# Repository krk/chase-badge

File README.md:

# chase-badge

Designed using [KiCad](https://kicad-pcb.org/).

I tried to follow datasheet recommendations and tried to base the design on application note schematics and PCB layouts of the active components.

First revision of the board in the repo is rev-8. Earlier revisions are not available in this repo.

Schematics contain notes and all components should have their datasheet in their details in KiCAD.

### Kudos

- to [@smcatala](https://github.com/smcatala) for reviewing the designs!

### Connectors

1. USB-C for power, charging and with bootloader programming.
2. FPC 4-pin for add-on boards.
3. Li-Po JST-SH 2-pin.

### Used ICs

##### ATTINY85V-20SU

- Chosen over ATTINY85V-10SU so we may support [bit-banged USB protocol](https://www.obdev.at/products/vusb/index.html) for programming the badge only with a USB cable. [datasheet](http://ww1.microchip.com/downloads/en/DeviceDoc/atmel-2586-avr-8-bit-microcontroller-attiny25-attiny45-attiny85_datasheet.pdf).

##### TLC6C9512PWR shift register

Chosen for low power consumption and low parts count. [datasheet](http://www.ti.com/lit/ds/symlink/tlc6c5912.pdf).

#### TPS63000 buck-boost regulator

[datasheet](http://www.ti.com/lit/ds/symlink/tps63000.pdf)

#### MCP73837-FCI_UN battery charge manager

[datasheet](http://ww1.microchip.com/downloads/en/DeviceDoc/20002071C.pdf)

### Tested

- Programming ATtiny85 with [Tiny AVR Programmer](https://www.sparkfun.com/products/11801)
- ATtiny85, TLC6C9512 and LEDs can work as expected when powered externally
- 3.3V or 5V is supported.

### Untested

- Power regulator
- Battery charge manager
- XSIG1 external signal, for supporting a buzzer, microphone etc.
- USB bootloader and programming from USB cable.

### TODO

1. Test everything under "untested" above.
2. Determine Li-Po battery size.

### PCB renders of rev-8

Note that some footprints are missing from the renders.

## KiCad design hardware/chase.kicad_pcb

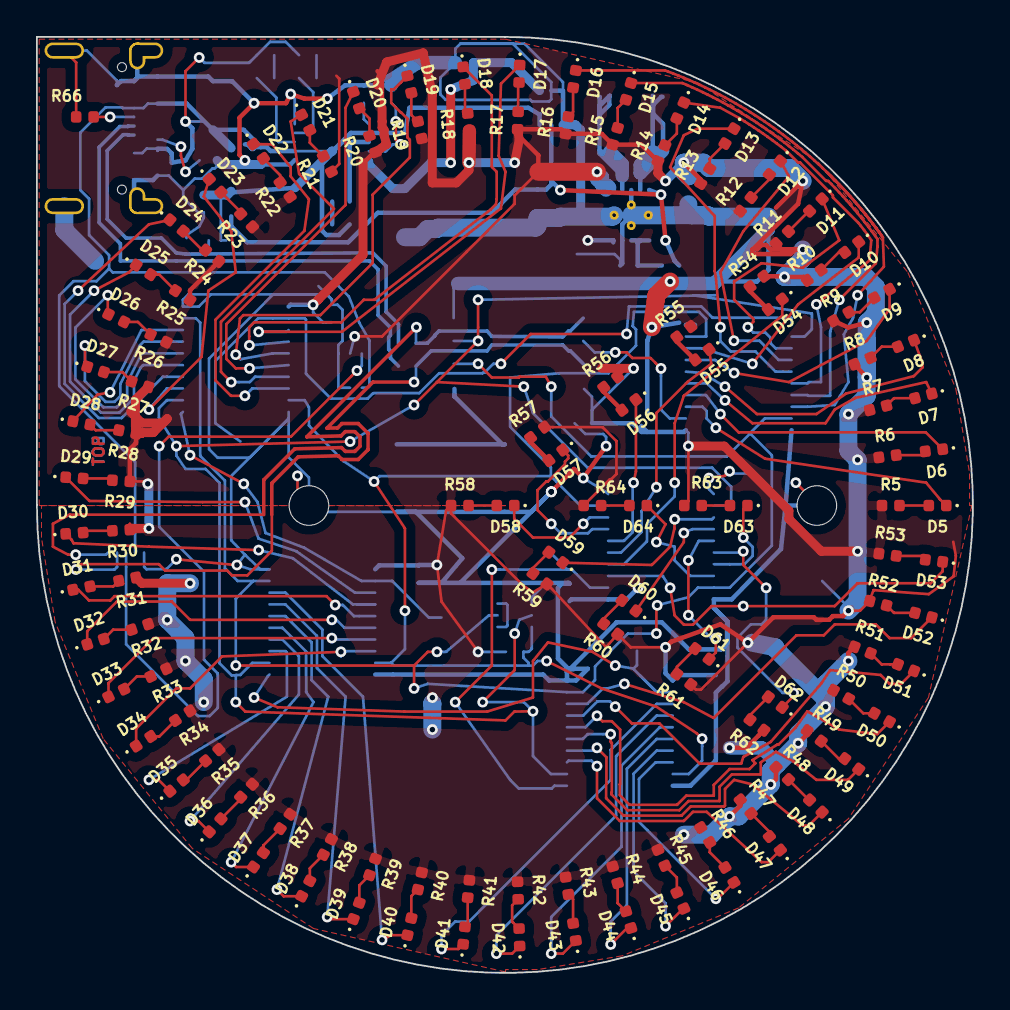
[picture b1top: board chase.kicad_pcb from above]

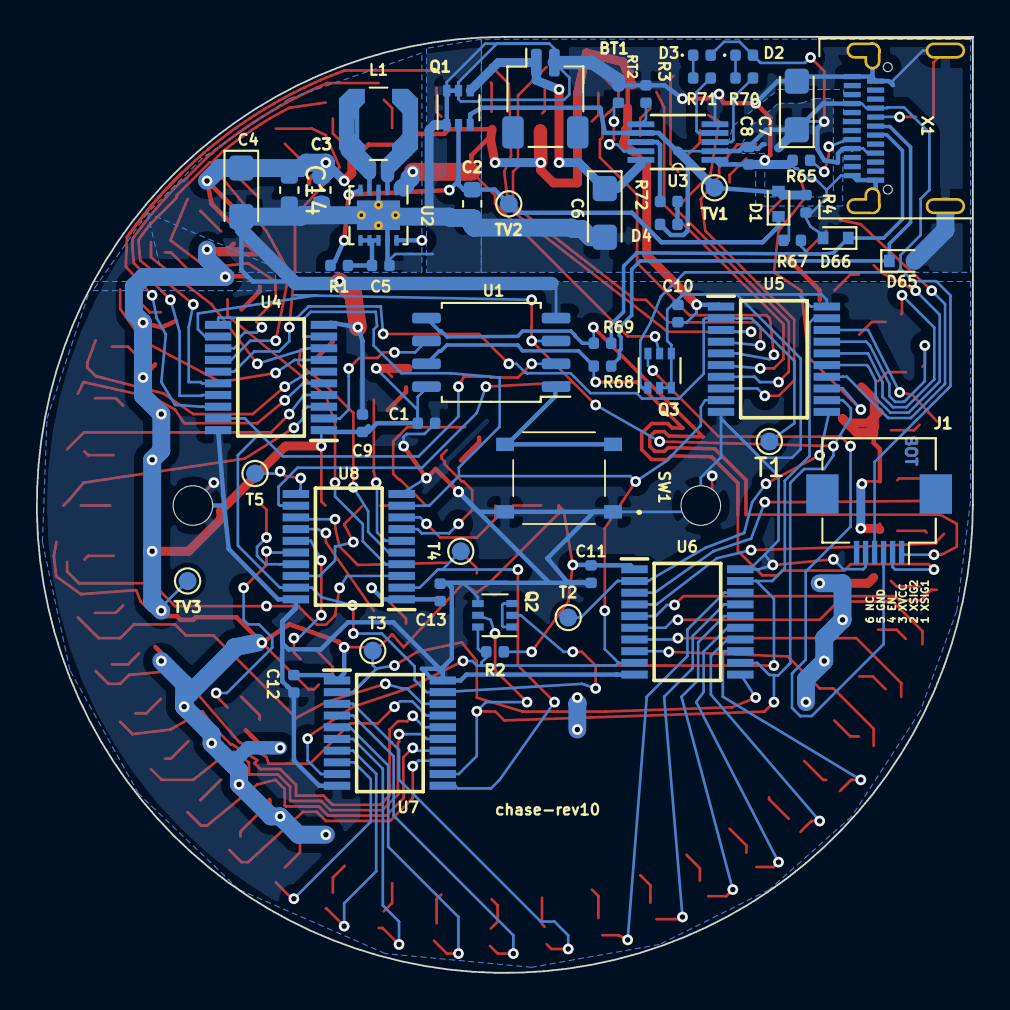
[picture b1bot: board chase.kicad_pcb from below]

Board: 2 copper layers, 52.0 x 52.0 mm, 179 parts (56 on the bottom side), 154 nets.

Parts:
BT1: Battery_Cell; JST_SH_SM02B-SRSS-TB_1x02-1MP_P1.00mm_Horizontal
C1, C5, C8, C9, C10, C11, C12, C13: 100n; C_0402_1005Metric
C2, C3, C14: 10uF; C_0603_1608Metric
C4, C6, C7: 47uF; CP_EIA-3216-18_Kemet-A
D1: D; D_SOD-523
D2, D3, D4, D5, D6, D7, D8, D9, D10, D11, D12, D13, D14, D15, D16, D17, D18, D19, D20, D21, D22, D23, D24, D25, D26, D27, D28, D29, D30, D31, D32, D33, D34, D35, D36, D37, D38, D39, D40, D41, D42, D43, D44, D45, D46, D47, D48, D49, D50, D51, D52, D53, D54, D55, D56, D57, D58, D59, D60, D61, D62, D63, D64: LED; LED_0402_1005Metric
D65, D66: 3V6; D_SOD-523
H1, H2: MountingHole_Pad; MountingHole_2.2mm_M2_ISO7380
J1: FH12-6S-0.5SH(55); Hirose_FH12-6S-0.5SH_1x06-1MP_P0.50mm_Horizontal
L1: 2.2uH; L_Coilcraft_LPS4018
Q1: DMC3400SDW-7; SOT-363_SC-70-6
Q2, Q3: DMN61D9UDW; SOT-363_SC-70-6
R1: 100; R_0402_1005Metric
R2, R5, R6, R7, R8, R9, R10, R11, R12, R13, R14, R15, R16, R17, R18, R19, R20, R21, R22, R23, R24, R25, R26, R27, R28, R29, R30, R31, R32, R33, R34, R35, R36, R37, R38, R39, R40, R41, R42, R43, R44, R45, R46, R47, R48, R49, R50, R51, R52, R53, R54, R55, R56, R57, R58, R59, R60, R61, R62, R63, R64, R70, R71, R72: 430; R_0402_1005Metric
R3: 1K; R_0402_1005Metric
R4: 100K; R_0402_1005Metric
R65, R66: 5.1K; R_0402_1005Metric
R67: 1K5; R_0402_1005Metric
R68, R69: 75.1; R_0402_1005Metric
RT2: 10K; R_0402_1005Metric
SW1: TS-1187A-B-A-B; TS1187ABAB
T1, T2, T3, T4, T5: TestPoint; TestPoint_Pad_D1.0mm
TV1, TV2, TV3: TestPoint; TestPoint_Pad_D1.0mm
U1: ATtiny85V; SOIC-8_5.275x5.275mm_P1.27mm
U2: TPS63000; Texas_DRC0010J_ThermalVias
U3: MCP73837-FCI_UN; SOP50P490X110-8N
U4, U5, U6, U7, U8: TLC6C5912GQPWRQ1; SOP65P640X120-20N
X1: USB3.1_TYPEC; Type-C_3.1_24P

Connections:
/LED Driver 1/RCK: Q2.5, U1.3, U4.12, U5.12, U6.12, U7.12, U8.12
/LED Driver 1/SER_IN: U1.6, U4.2
/LED Driver 1/SRCK: Q2.2, U1.2, U4.19, U5.19, U6.19, U7.19, U8.19
/LED Driver 1/~CLR: Q2.6, R2.1, U4.9, U5.9, U6.9, U7.9, U8.9
/LED Driver 2/SER_IN: T1.1, U4.11, U5.2
/LED Driver 3/SER_IN: T2.1, U5.11, U6.2
/LED Driver 4/SER_IN: T3.1, U6.11, U7.2
/LED Driver 5/SER_IN: T4.1, U7.11, U8.2
/LED Driver 5/SER_OUT: T5.1, U8.11
/USBD+: D65.1, R68.2, X1.B6
/USBD-: D66.1, R67.1, R69.2, X1.B7
D+: J1.2, R68.1, U1.7
D-: J1.1, R69.1, U1.5
GND: BT1.2, C1.2, C2.2, C3.2, C4.2, C5.1, C6.2, C7.2, C8.1, C9.1, C10.1, C11.1, C12.1, C13.1, C14.2, D65.2, D66.2, H1.1, H2.1, J1.5, Q1.1, Q1.5, Q1.6, Q2.4, Q3.2, Q3.3, Q3.4, R3.2, R4.1, R65.1, R66.1, RT2.1, SW1.A1, SW1.B1, U1.4, U2.3, U2.9, U2.11, U3.1, U3.5, U4.10, U4.20, U5.10, U5.20, U6.10, U6.20, U7.10, U7.20, U8.10, U8.20, X1.A1, X1.A12, X1.B1, X1.B12, X1.SHELL
unnamed: BT1.1, C6.1, Q1.4, U3.10
unnamed: C5.2, R1.1, U2.6, U2.7, U2.8
unnamed: D2.1, R70.2
unnamed: D3.1, R71.2
unnamed: D4.1, R72.2
unnamed: D5.1, U4.3
unnamed: D5.2, R5.2
unnamed: D6.1, U4.4
unnamed: D6.2, R6.2
unnamed: D7.1, U4.5
unnamed: D7.2, R7.2
unnamed: D8.1, U4.6
unnamed: D8.2, R8.2
unnamed: D9.1, U4.7
unnamed: D9.2, R9.2
unnamed: D10.1, U4.8
unnamed: D10.2, R10.2
unnamed: D11.1, U4.13
unnamed: D11.2, R11.2
unnamed: D12.1, U4.14
unnamed: D12.2, R12.2
unnamed: D13.1, U4.15
unnamed: D13.2, R13.2
unnamed: D14.1, U4.16
unnamed: D14.2, R14.2
unnamed: D15.1, U4.17
unnamed: D15.2, R15.2
unnamed: D16.1, U4.18
unnamed: D16.2, R16.2
unnamed: D17.1, U5.3
unnamed: D17.2, R17.2
unnamed: D18.1, U5.4
unnamed: D18.2, R18.2
unnamed: D19.1, U5.5
unnamed: D19.2, R19.2
unnamed: D20.1, U5.6
unnamed: D20.2, R20.2
unnamed: D21.1, U5.7
unnamed: D21.2, R21.2
unnamed: D22.1, U5.8
unnamed: D22.2, R22.2
unnamed: D23.1, U5.13
unnamed: D23.2, R23.2
unnamed: D24.1, U5.14
unnamed: D24.2, R24.2
unnamed: D25.1, U5.15
unnamed: D25.2, R25.2
unnamed: D26.1, U5.16
unnamed: D26.2, R26.2
unnamed: D27.1, U5.17
unnamed: D27.2, R27.2
unnamed: D28.1, U5.18
unnamed: D28.2, R28.2
unnamed: D29.1, U6.3
unnamed: D29.2, R29.2
unnamed: D30.1, U6.4
unnamed: D30.2, R30.2
unnamed: D31.1, U6.5
unnamed: D31.2, R31.2
unnamed: D32.1, U6.6
unnamed: D32.2, R32.2
unnamed: D33.1, U6.7
unnamed: D33.2, R33.2
unnamed: D34.1, U6.8
unnamed: D34.2, R34.2
unnamed: D35.1, U6.13
unnamed: D35.2, R35.2
unnamed: D36.1, U6.14
unnamed: D36.2, R36.2
unnamed: D37.1, U6.15
unnamed: D37.2, R37.2
unnamed: D38.1, U6.16
unnamed: D38.2, R38.2
unnamed: D39.1, U6.17
unnamed: D39.2, R39.2
unnamed: D40.1, U6.18
unnamed: D40.2, R40.2
unnamed: D41.1, U7.3
unnamed: D41.2, R41.2
unnamed: D42.1, U7.4
unnamed: D42.2, R42.2
unnamed: D43.1, U7.5
unnamed: D43.2, R43.2
unnamed: D44.1, U7.6
unnamed: D44.2, R44.2
unnamed: D45.1, U7.7
unnamed: D45.2, R45.2
unnamed: D46.1, U7.8
unnamed: D46.2, R46.2
unnamed: D47.1, U7.13
unnamed: D47.2, R47.2
unnamed: D48.1, U7.14
unnamed: D48.2, R48.2
unnamed: D49.1, U7.15
unnamed: D49.2, R49.2
unnamed: D50.1, U7.16
unnamed: D50.2, R50.2
unnamed: D51.1, U7.17
unnamed: D51.2, R51.2
unnamed: D52.1, U7.18
unnamed: D52.2, R52.2
unnamed: D53.1, U8.3
unnamed: D53.2, R53.2
unnamed: D54.1, U8.4
unnamed: D54.2, R54.2
unnamed: D55.1, U8.5
unnamed: D55.2, R55.2
unnamed: D56.1, U8.6
unnamed: D56.2, R56.2
unnamed: D57.1, U8.7
unnamed: D57.2, R57.2
unnamed: D58.1, U8.8
unnamed: D58.2, R58.2
unnamed: D59.1, U8.13
unnamed: D59.2, R59.2
unnamed: D60.1, U8.14
unnamed: D60.2, R60.2
unnamed: D61.1, U8.15
unnamed: D61.2, R61.2
unnamed: D62.1, U8.16
unnamed: D62.2, R62.2
unnamed: D63.1, U8.17
unnamed: D63.2, R63.2
unnamed: D64.1, U8.18
unnamed: D64.2, R64.2
unnamed: L1.1, U2.4
unnamed: L1.2, U2.2
unnamed: Q2.1, Q2.3
unnamed: R3.1, U3.6
unnamed: R65.2, X1.A5
unnamed: R66.2, X1.B5
unnamed: R70.1, U3.3
unnamed: R71.1, U3.4
unnamed: R72.1, U3.8
unnamed: RT2.2, U3.9
unnamed: SW1.C1, SW1.D1, U1.1
VBATOUT: C2.1, D1.1, Q1.2, R1.2, TV2.1, U2.5
VBUS: C7.1, C8.2, D1.2, D2.2, D3.2, D4.2, J1.4, Q1.3, Q3.1, R4.2, R67.2, TV1.1, U3.2, U3.7, X1.A4, X1.A9, X1.B4, X1.B9
VCC: C1.1, C3.1, C4.1, C9.2, C10.2, C11.2, C12.2, C13.2, C14.1, Q3.5, R2.2, R5.1, R6.1, R7.1, R8.1, R9.1, R10.1, R11.1, R12.1, R13.1, R14.1, R15.1, R16.1, R17.1, R18.1, R19.1, R20.1, R21.1, R22.1, R23.1, R24.1, R25.1, R26.1, R27.1, R28.1, R29.1, R30.1, R31.1, R32.1, R33.1, R34.1, R35.1, R36.1, R37.1, R38.1, R39.1, R40.1, R41.1, R42.1, R43.1, R44.1, R45.1, R46.1, R47.1, R48.1, R49.1, R50.1, R51.1, R52.1, R53.1, R54.1, R55.1, R56.1, R57.1, R58.1, R59.1, R60.1, R61.1, R62.1, R63.1, R64.1, TV3.1, U1.8, U2.1, U2.10, U4.1, U5.1, U6.1, U7.1, U8.1
XVCC: J1.3, Q3.6

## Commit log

2020-02-20 Import chase-v8.
2020-02-21 Replace J1 with 6 pin connector, use cheaper resistor for 430 ohms.
2020-02-24 Change TPS63000 variable to TPS63001 3.3V buck-boost.
    TPS630001 is in stock now, can use it again. R73 and R74 are not
    necessary now.
    Change resistor brand for 71.5ohm resistors.
    From VikingTech to UniRoyal which is cheaper.
2020-02-24 Add fabrication BOM files.
